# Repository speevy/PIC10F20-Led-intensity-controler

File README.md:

# Led intensity controler for IKEA JANSJÖ using PIC 10F200

This project is for improving the IKEA JANSJÖ led light with power control. Includes both software and hardware design.

I have build myself the circuit using a prototyping board of 15 x 4 tenths of an inch, that fits inside the original lamp switch.

I have also designed a 2 layer pcb board for smd components with micro-usb port for programming the pic. (Not tested yet, boards are on the way)

It consist of two push-buttons, one for increasing power, and another for decreasing. Pressing the two buttons at the same time switches on and off the ligth.

The design can be adapted for use in other similar applications. Be aware on the voltage and current of the device.

**WARNING!** There are two kinds of power suppliers for LED lamps: Voltage sources and current sources. This design is *ONLY* meant for the Voltage sources.

_UPDATE_: Having seen the teardown of the device in this video: https://www.youtube.com/watch?v=H4aymFmak9Y I realized that although this circuit is powered by a voltage source, is later converted to current source to drive the LED.

Having seen the comments on the video, seems that the main point of failure of the lamp are the switches (already fixed that ;)) and the power supply. There also seem that the driver chips are able to work at 5V, so the design could be rebuild to power the lamp from uUSB connector, using standard USB power supplies.

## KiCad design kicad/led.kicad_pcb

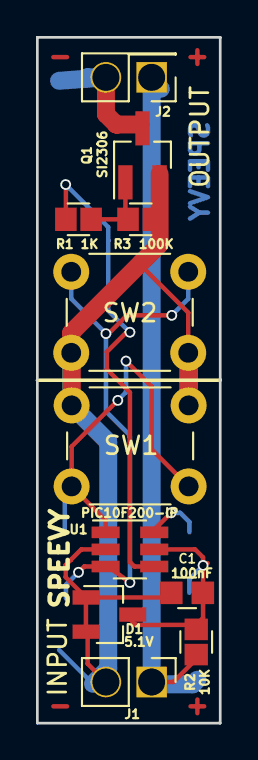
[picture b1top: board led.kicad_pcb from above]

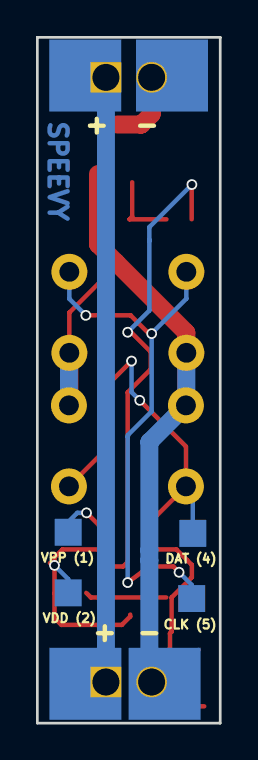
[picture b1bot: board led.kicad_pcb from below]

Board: 2 copper layers, 10.2 x 38.1 mm, 15 parts (4 on the bottom side), 9 nets.

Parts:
C1: 100nF; C_0805
D1: 5.1V; D_SOT-23_ANK
J1: INPUT; Pin_Header_Straight_1x02_Pitch2.54mm
J2: OUTPUT; Pin_Header_Straight_2x01_Pitch2.54mm
J3: VDD (2); Measurement_Point_Square-SMD-Pad_Small
J4: VPP (1); Measurement_Point_Square-SMD-Pad_Small
J5: DAT (4); Measurement_Point_Square-SMD-Pad_Small
J6: CLK (5); Measurement_Point_Square-SMD-Pad_Small
Q1: SI2306; SOT-23_Handsoldering
R1: 1K; R_0805
R2: 10K; R_0805
R3: 100K; R_0805
SW1: SW DOWN; SW_PUSH_6mm_h7.3mm
SW2: SW UP; SW_PUSH_6mm_h7.3mm
U1: PIC10F200-IP; SOT-23-6_Handsoldering

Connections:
GNDD: C1.1, D1.2, J1.2, Q1.2, R3.1, SW1.1, SW2.1, U1.2
unnamed: C1.2, D1.1, J3.1, R2.2, U1.5
unnamed: J2.2, Q1.3
unnamed: J4.1, U1.6
unnamed: J5.1, SW1.2, U1.1
unnamed: J6.1, SW2.2, U1.3
unnamed: Q1.1, R1.1, R3.2
unnamed: R1.2, U1.4
VDD: J1.1, J2.1, R2.1

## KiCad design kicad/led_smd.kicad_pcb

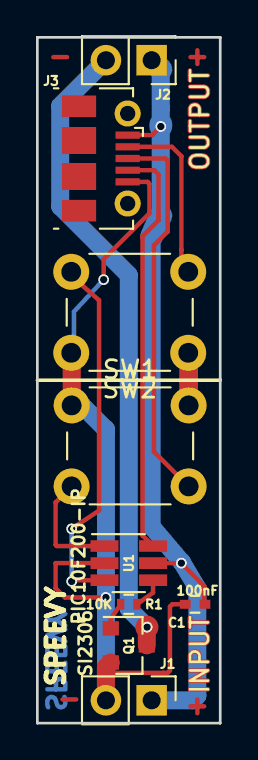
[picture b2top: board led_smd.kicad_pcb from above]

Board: 2 copper layers, 10.2 x 38.1 mm, 9 parts (0 on the bottom side), 8 nets.

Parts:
C1: 100nF; C_0402
J1: INPUT; Pin_Header_Straight_1x02_Pitch2.54mm
J2: OUTPUT; Pin_Header_Straight_2x01_Pitch2.54mm
J3: USB_OTG; USB_Micro-B_Molex-105017-0001
Q1: SI2306; SOT-23
R1: 10K; R_0402
SW1: SW DOWN; SW_PUSH_6mm_h7.3mm
SW2: SW UP; SW_PUSH_6mm_h7.3mm
U1: PIC10F200-IP; SOT-23-6_Handsoldering

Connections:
GNDD: C1.2, J1.2, J3.5, Q1.2, SW1.1, SW2.1, U1.2
unnamed: J2.2, Q1.3
unnamed: J3.2, SW2.2, U1.3
unnamed: J3.3, SW1.2, U1.1
unnamed: J3.4, U1.6
unnamed: Q1.1, R1.1
unnamed: R1.2, U1.4
VDD: C1.1, J1.1, J2.1, J3.1, U1.5

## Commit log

2018-03-25 Refactor + improve button detection
2018-03-25 Non-linear duty cicle
2018-03-25 Schematic + PCB WiP
2018-03-30 Schematic + PCB SMD WiP
2018-04-07 Schematic + PCB SMD new version
2018-04-07 New version of the algorithm: - less steps and lesss power for first step - pushing both buttons powers on(near full power)/off. - power off pushing both buttons is now the same state as going to pow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
2018-04-21 Refactor of the duty cicle algorithm (now first value is minimum, and value 0 is power off). Added comments.
2019-12-30 Added a diode to isolate "power" VDD to microcontroler VDD. Changed some footprints to enable bigger resistor and capacitor. Moved a bit the headers in order to fit. Added extra soldering pads to VIN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
2019-12-30 minor fixes
2019-12-30 Added GPL v2 LICENCE file
2021-07-27 Modified to allow input voltages > 5V. Also removed micro usb connector for programming, and added some test points in its place.
